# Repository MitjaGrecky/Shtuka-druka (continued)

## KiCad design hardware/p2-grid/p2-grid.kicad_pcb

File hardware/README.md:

# Hardware

KiCad 10 projects. Each board is generated by Python scripts in its `gen/` folder; CI (`.github/workflows/kicad.yml`)
runs ERC, DRC with schematic parity and exports BOM, Gerbers and placement files on every push.
Board map and reasoning: `docs/ru/29_board_map.md`.

| Board | What | Status | Spec |
|---|---|---|---|
| [`m1-screen-knobs`](m1-screen-knobs/) | 8 encoders with touch and 13-LED rings under the screen | rev 0.1, routing (see `UNROUTED`, `QUILTER.md`) | `docs/ru/30_m1_screen_knobs.md` |
| [`bb1-battery`](bb1-battery/) | Battery board: 6 cells, 2 x BQ7791500 (replaces BM, P143-P146) | rev 0.3, placed | `bb1-battery/README.md` |
| [`w1-levels`](w1-levels/) | Volume pots, P48 buttons, window for M5 | rev 0.1, routed | `docs/ru/31_w1_levels.md` |

License: CERN Open Hardware Licence Version 2 - Strongly Reciprocal (CERN-OHL-S-2.0), see `LICENSE`.

Replaced boards are not kept in the tree (P150, 25.11.2026): BM 0.3 (`bm-bms3s`, replaced by BB1, P143, P144) is in the git history only; BB1 carries its protection circuit in `bb1-battery/gen/bm_circuit.py`.

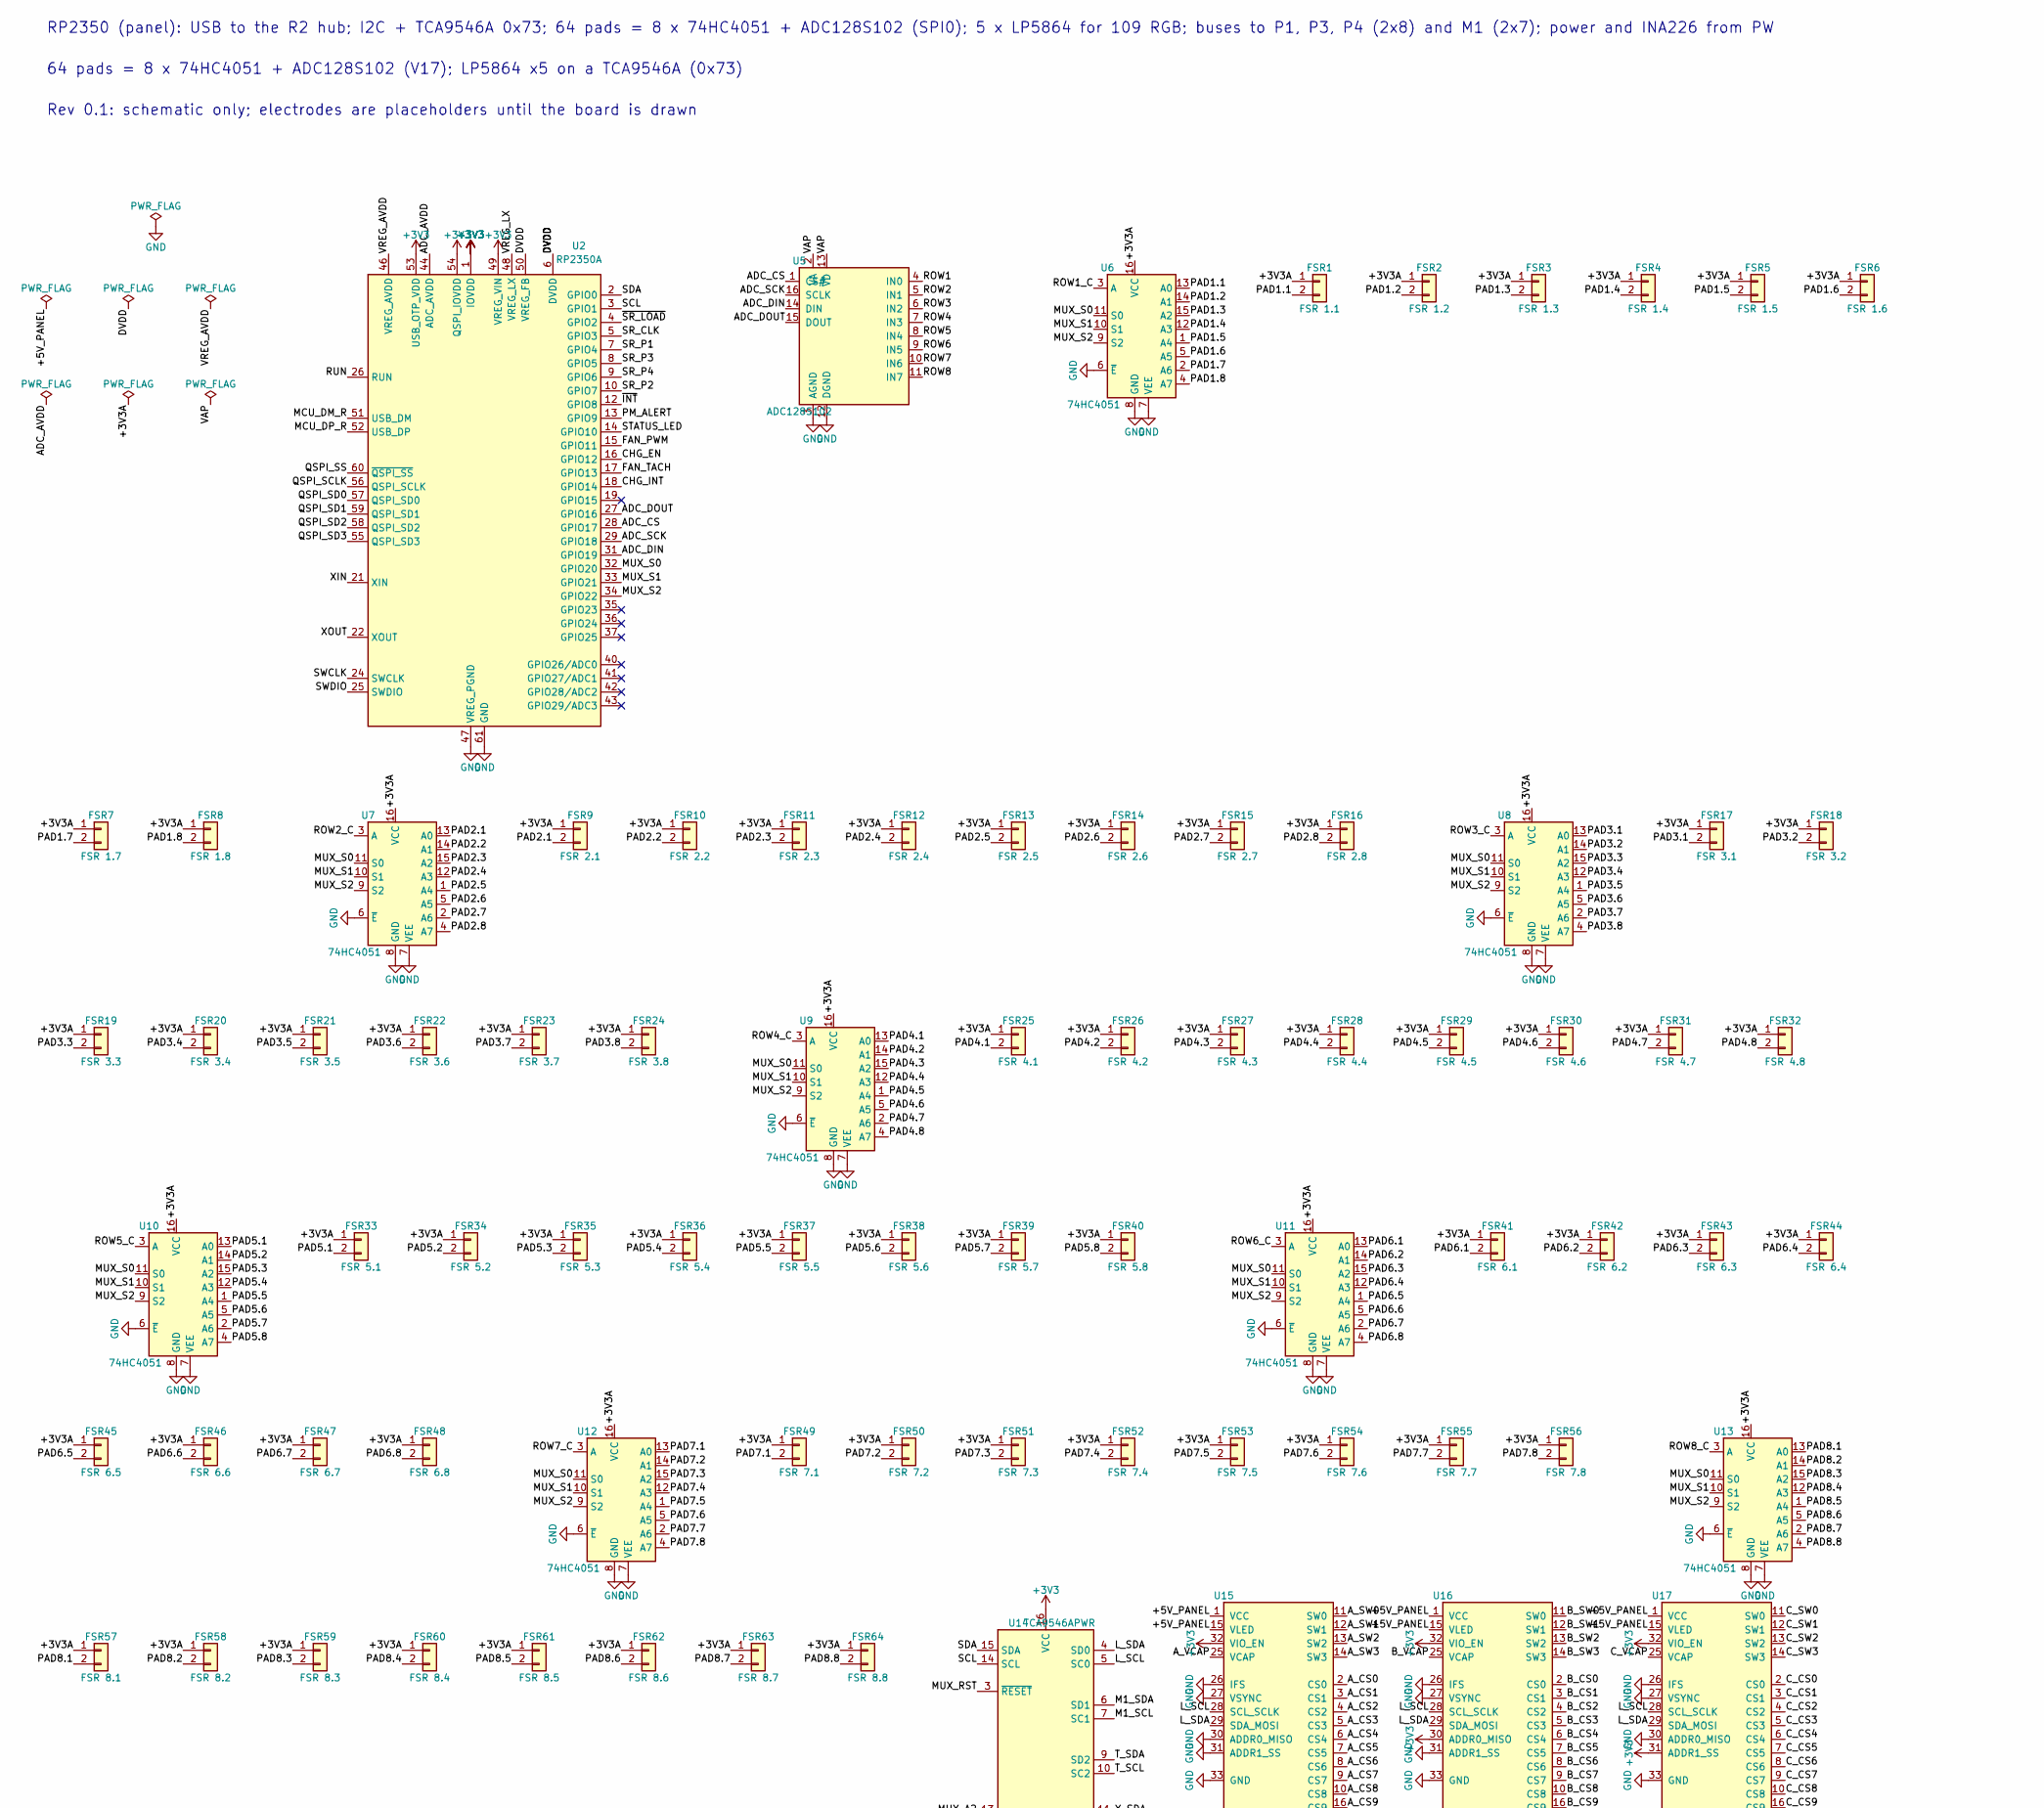
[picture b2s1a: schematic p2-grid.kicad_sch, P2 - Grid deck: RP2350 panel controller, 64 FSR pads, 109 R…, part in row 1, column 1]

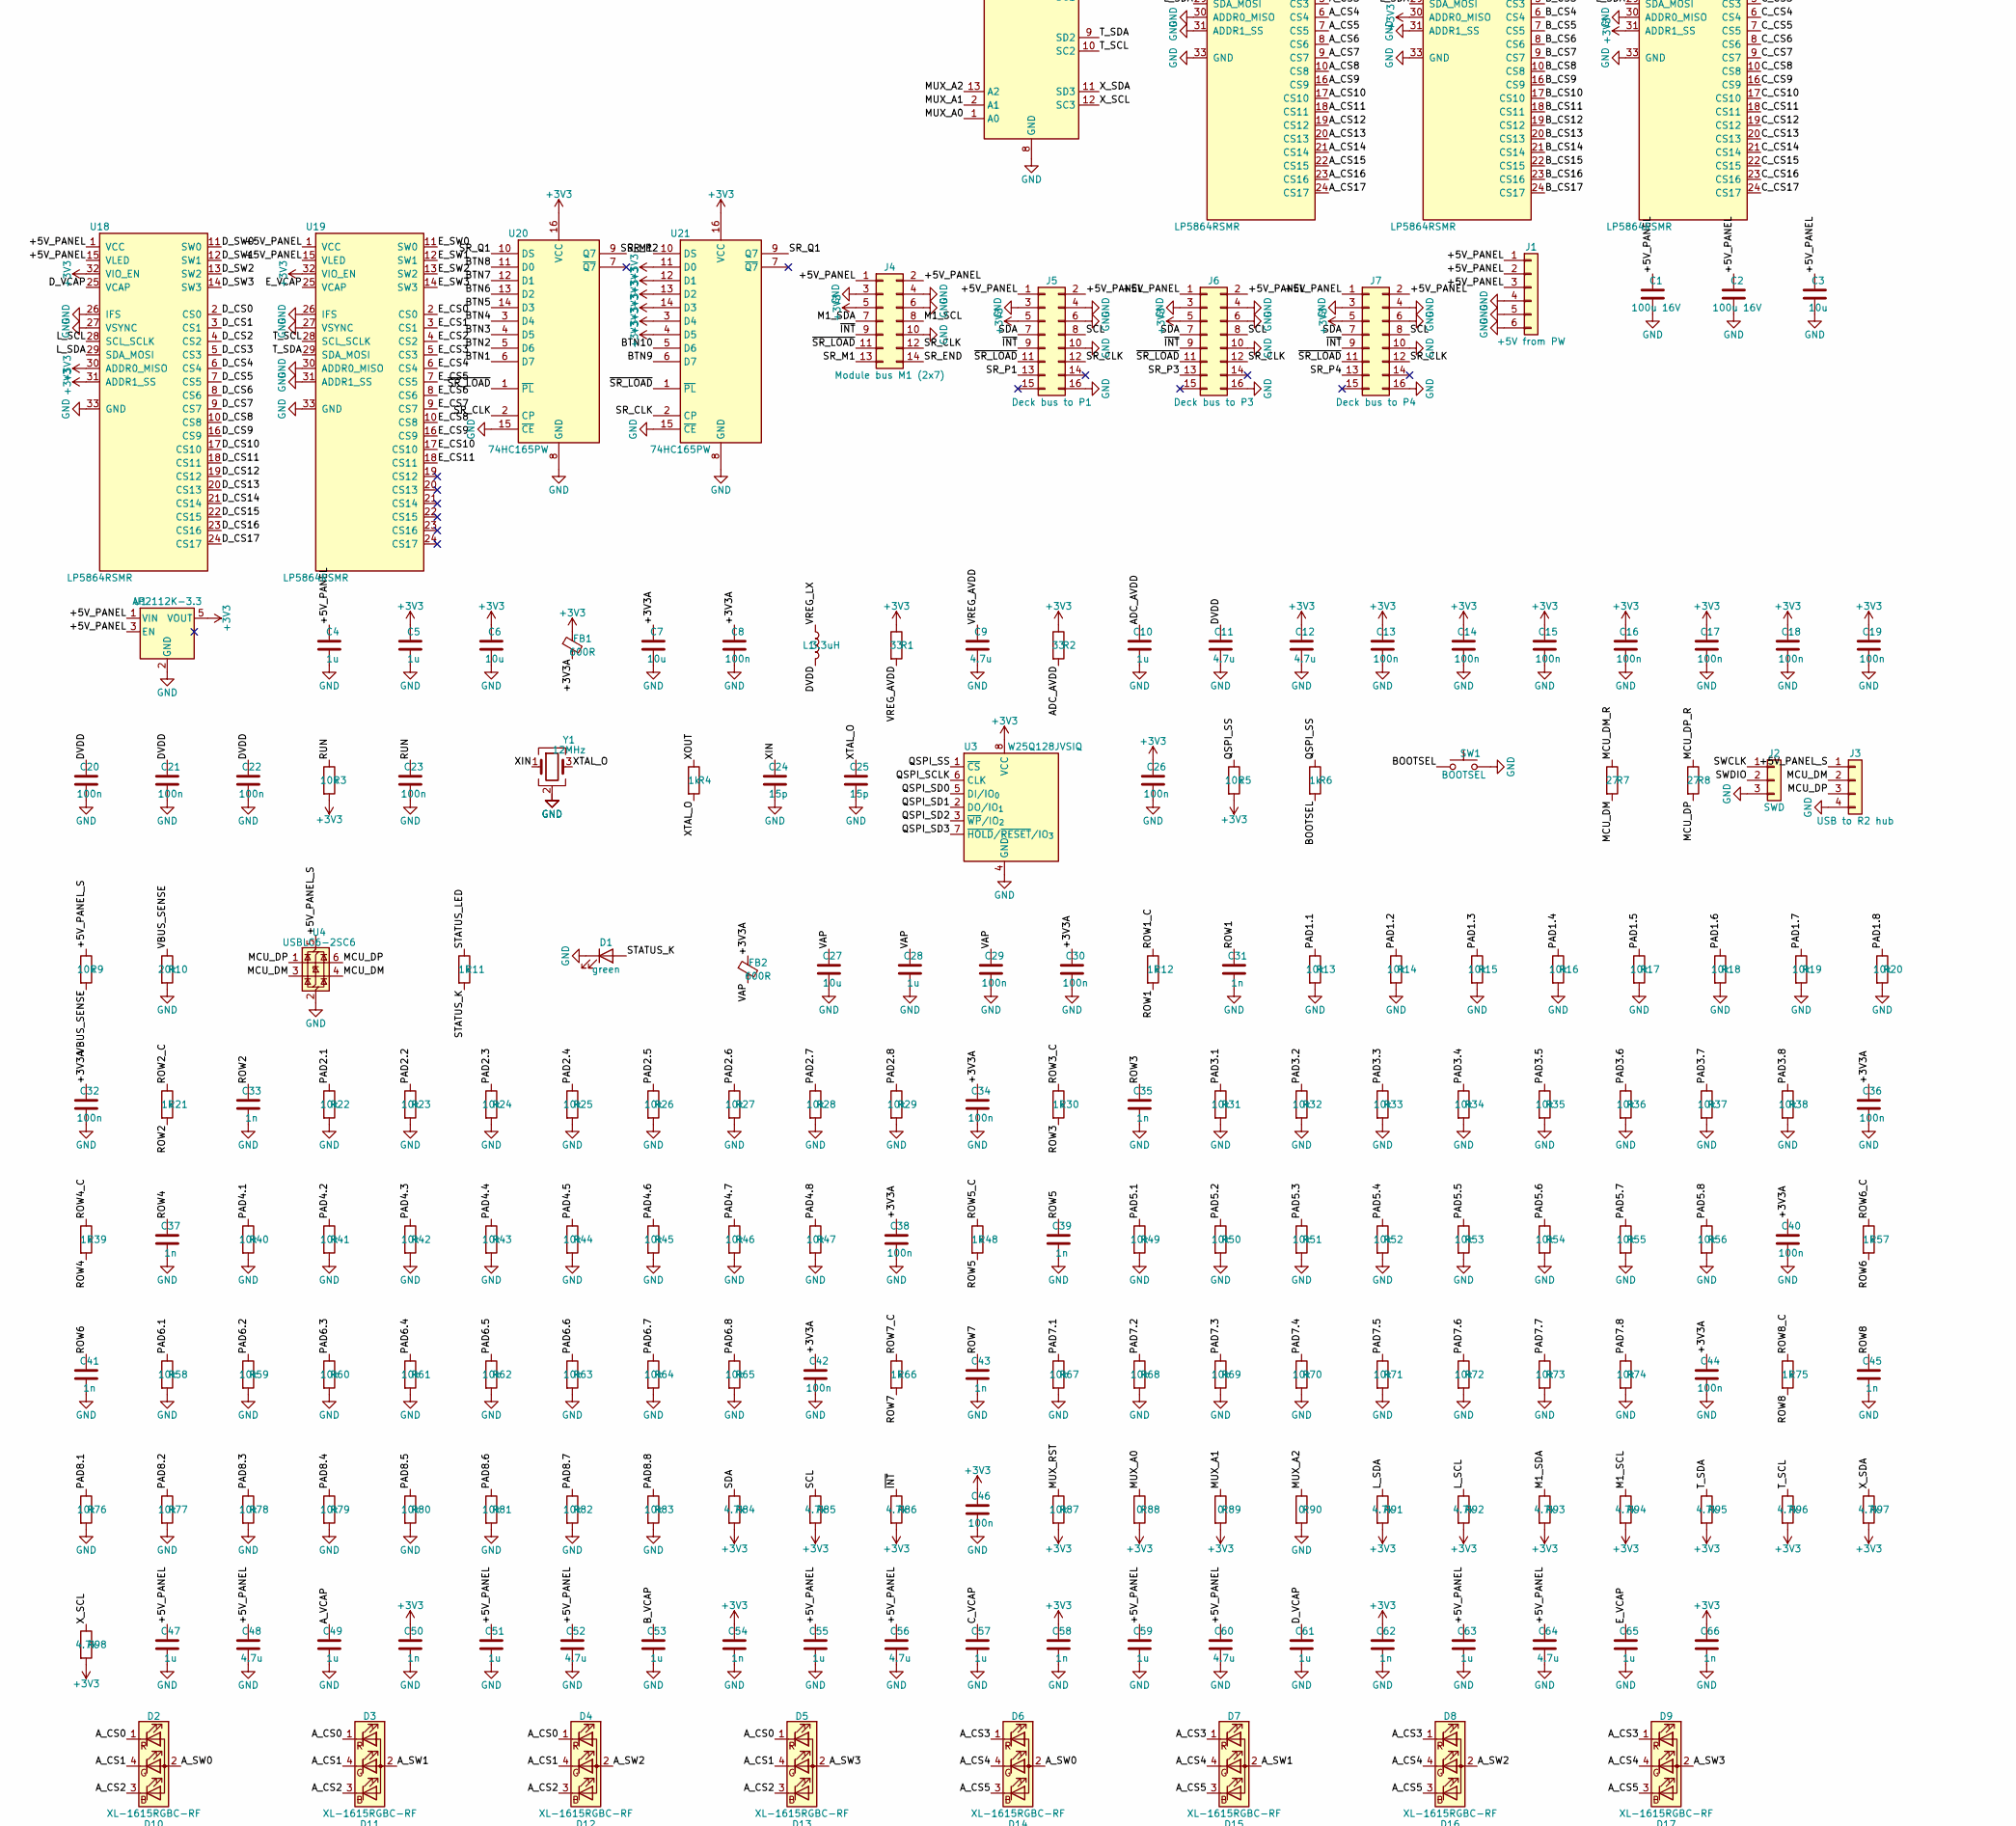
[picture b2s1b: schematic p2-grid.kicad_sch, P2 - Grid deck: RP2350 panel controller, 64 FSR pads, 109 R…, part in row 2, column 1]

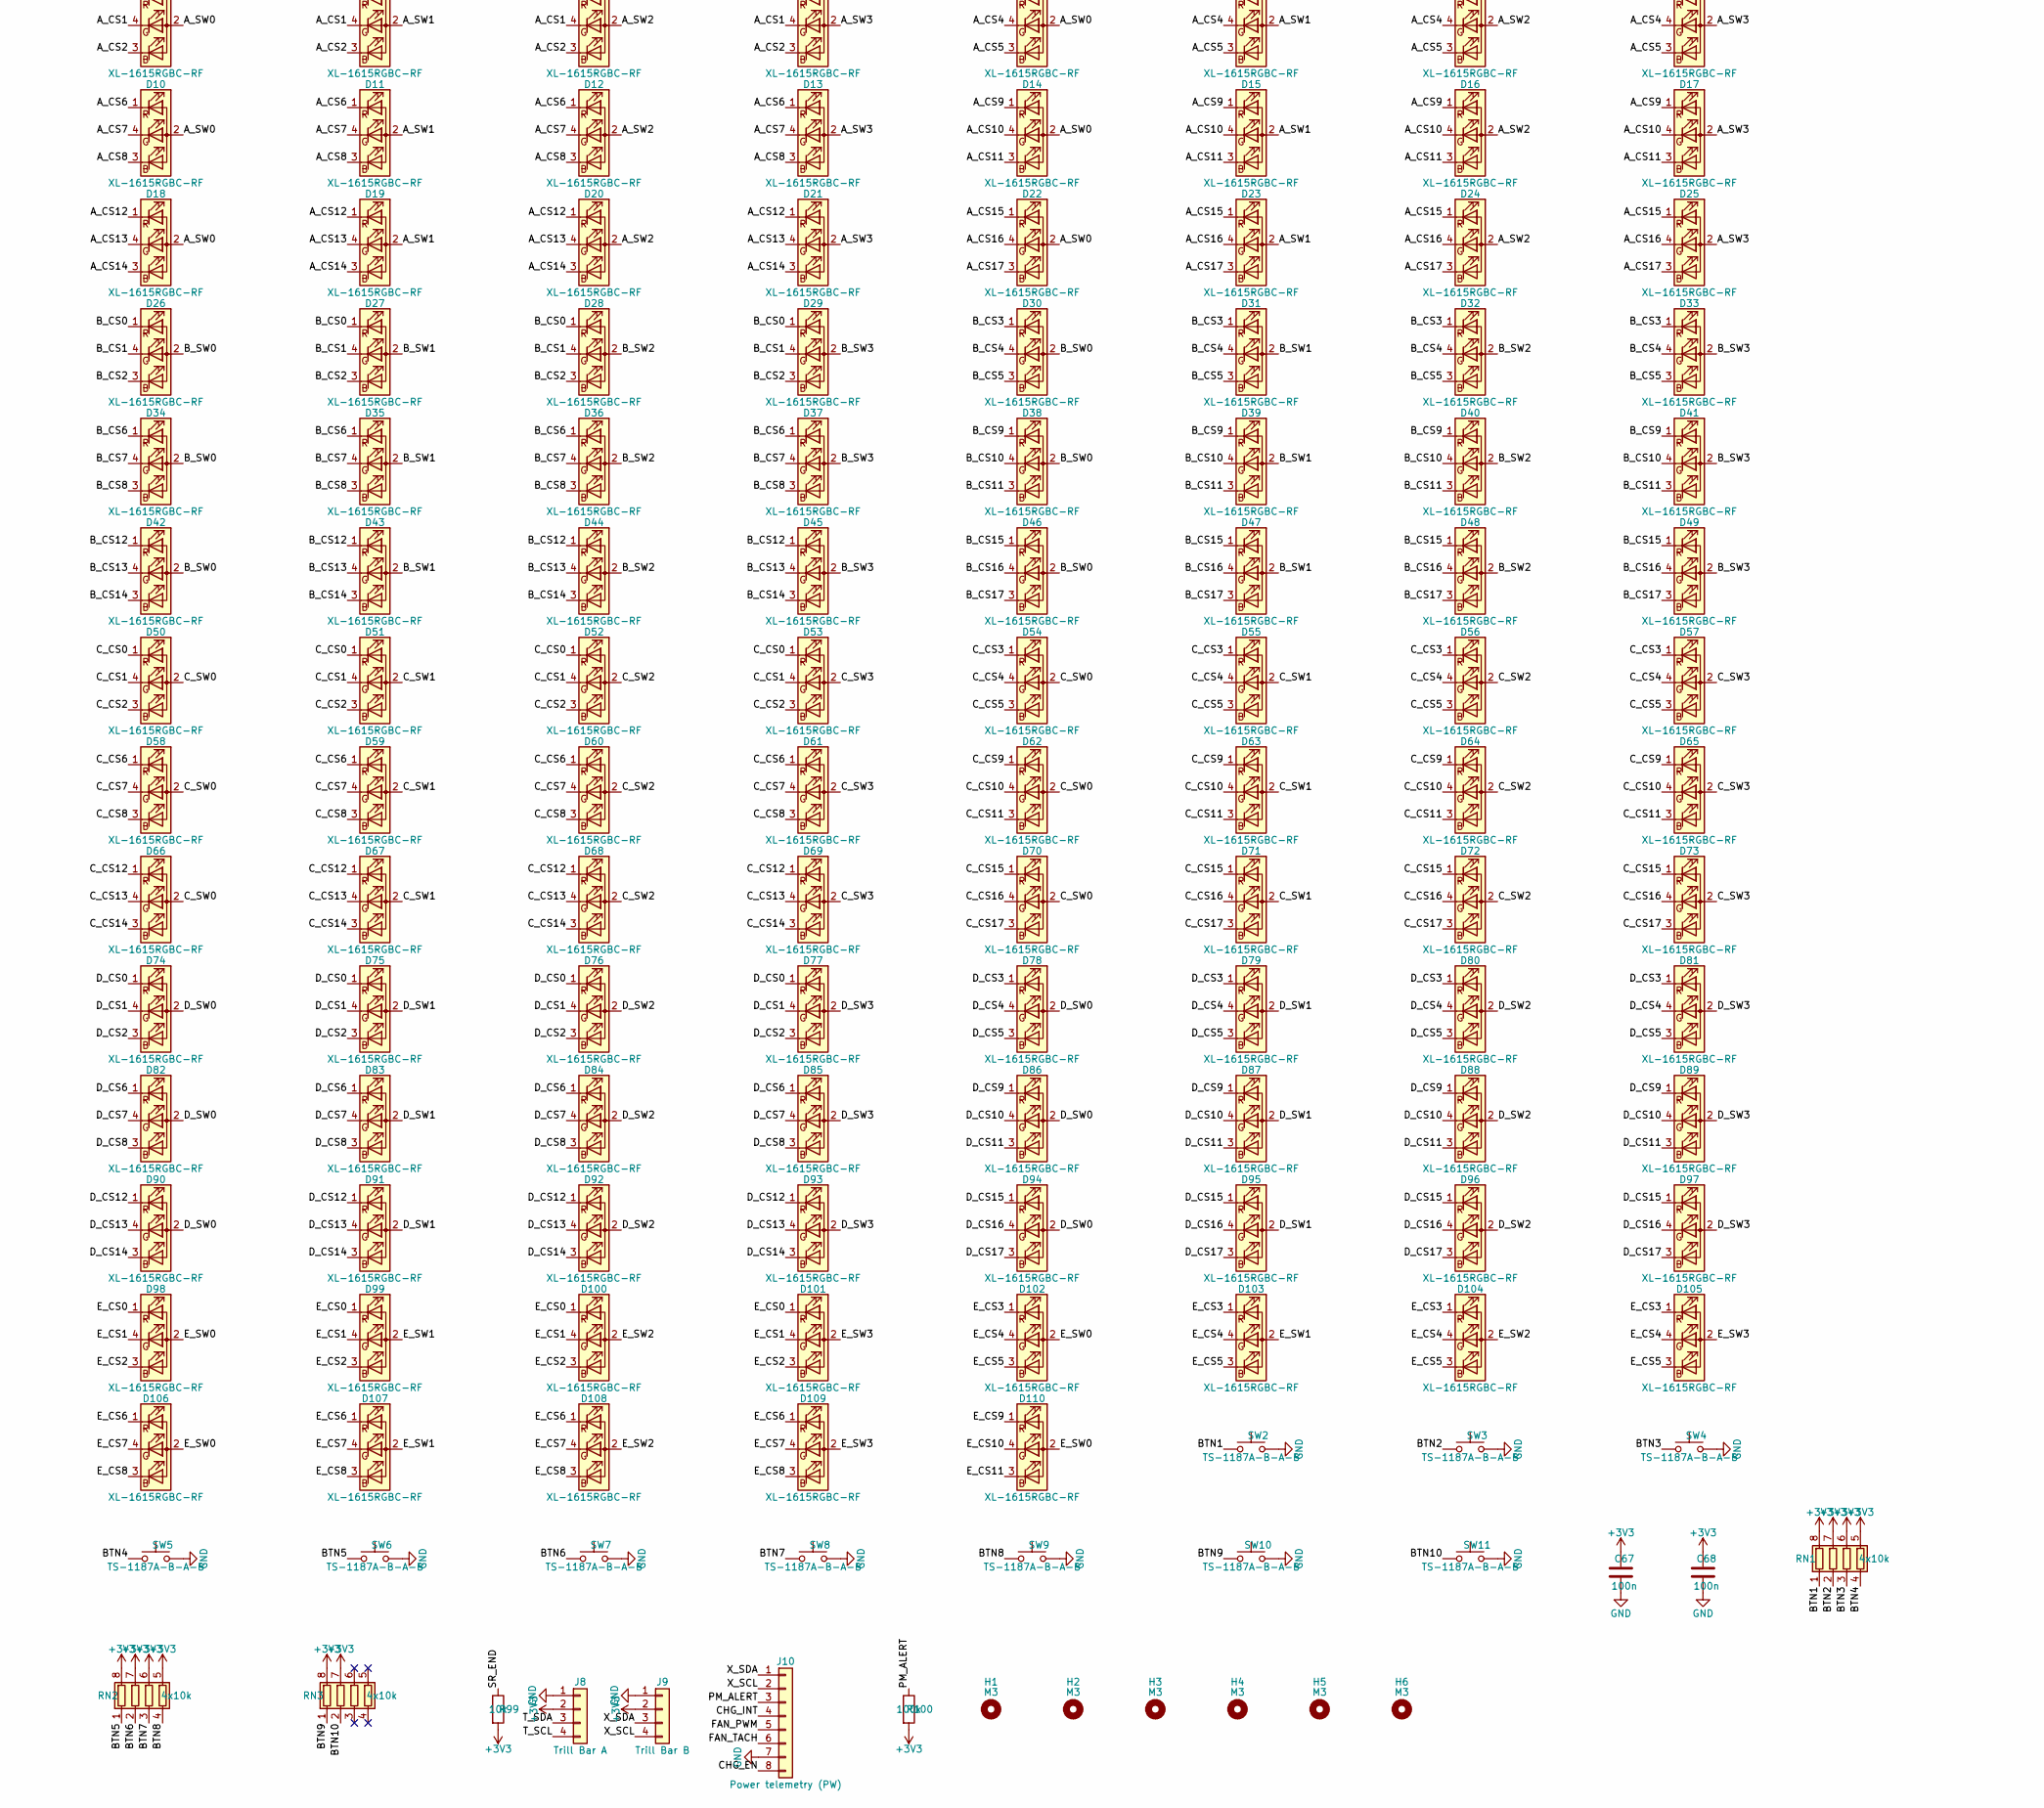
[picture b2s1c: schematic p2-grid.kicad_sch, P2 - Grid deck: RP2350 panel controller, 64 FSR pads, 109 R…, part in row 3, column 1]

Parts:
C1, C2: 100u 16V; CP_Elec_6.3x5.4; LCSC C7469977
C3, C6, C7, C27: 10u; C_0805_2012Metric; LCSC C15850
C4, C5: 1u; C_0603_1608Metric; LCSC C52923
C8, C13, C14, C15, C16, C17, C18, C19, C20, C21, C22, C23, C26, C29, C30, C32, C34, C36, C38, C40, C42, C44, C46, C67, C68: 100n; C_0402_1005Metric; LCSC C1525
C9, C11, C12, C48, C52, C56, C60, C64: 4.7u; C_0805_2012Metric; LCSC C1779
C10, C28, C47, C49, C51, C53, C55, C57, C59, C61, C63, C65: 1u; C_0402_1005Metric; LCSC C52923
C24, C25: 15p; C_0402_1005Metric
C31, C33, C35, C37, C39, C41, C43, C45, C50, C54, C58, C62, C66: 1n; C_0402_1005Metric; LCSC C1523
D1: green; LED_0603_1608Metric; LCSC C84267
D2, D3, D4, D5, D6, D7, D8, D9, D10, D11, D12, D13, D14, D15, D16, D17, D18, D19, D20, D21, D22, D23, D24, D25, D26, D27, D28, D29, D30, D31, D32, D33, D34, D35, D36, D37, D38, D39, D40, D41, D42, D43, D44, D45, D46, D47, D48, D49, D50, D51, D52, D53, D54, D55, D56, D57, D58, D59, D60, D61, D62, D63, D64, D65, D66, D67, D68, D69, D70, D71, D72, D73, D74, D75, D76, D77, D78, D79, D80, D81, D82, D83, D84, D85, D86, D87, D88, D89, D90, D91, D92, D93, D94, D95, D96, D97, D98, D99, D100, D101, D102, D103, D104, D105, D106, D107, D108, D109, D110: XL-1615RGBC-RF; LED_RGB_XL-1615RGBC_1.6x1.5mm; LCSC C965840
FB1, FB2: 600R; R_0603_1608Metric; LCSC C14709
FSR1: FSR 1.1; TestPoint_2Pads_Pitch2.54mm_Drill0.8mm
FSR2: FSR 1.2; TestPoint_2Pads_Pitch2.54mm_Drill0.8mm
FSR3: FSR 1.3; TestPoint_2Pads_Pitch2.54mm_Drill0.8mm
FSR4: FSR 1.4; TestPoint_2Pads_Pitch2.54mm_Drill0.8mm
FSR5: FSR 1.5; TestPoint_2Pads_Pitch2.54mm_Drill0.8mm
FSR6: FSR 1.6; TestPoint_2Pads_Pitch2.54mm_Drill0.8mm
FSR7: FSR 1.7; TestPoint_2Pads_Pitch2.54mm_Drill0.8mm
FSR8: FSR 1.8; TestPoint_2Pads_Pitch2.54mm_Drill0.8mm
FSR9: FSR 2.1; TestPoint_2Pads_Pitch2.54mm_Drill0.8mm
FSR10: FSR 2.2; TestPoint_2Pads_Pitch2.54mm_Drill0.8mm
FSR11: FSR 2.3; TestPoint_2Pads_Pitch2.54mm_Drill0.8mm
FSR12: FSR 2.4; TestPoint_2Pads_Pitch2.54mm_Drill0.8mm
FSR13: FSR 2.5; TestPoint_2Pads_Pitch2.54mm_Drill0.8mm
FSR14: FSR 2.6; TestPoint_2Pads_Pitch2.54mm_Drill0.8mm
FSR15: FSR 2.7; TestPoint_2Pads_Pitch2.54mm_Drill0.8mm
FSR16: FSR 2.8; TestPoint_2Pads_Pitch2.54mm_Drill0.8mm
FSR17: FSR 3.1; TestPoint_2Pads_Pitch2.54mm_Drill0.8mm
FSR18: FSR 3.2; TestPoint_2Pads_Pitch2.54mm_Drill0.8mm
FSR19: FSR 3.3; TestPoint_2Pads_Pitch2.54mm_Drill0.8mm
FSR20: FSR 3.4; TestPoint_2Pads_Pitch2.54mm_Drill0.8mm
FSR21: FSR 3.5; TestPoint_2Pads_Pitch2.54mm_Drill0.8mm
FSR22: FSR 3.6; TestPoint_2Pads_Pitch2.54mm_Drill0.8mm
FSR23: FSR 3.7; TestPoint_2Pads_Pitch2.54mm_Drill0.8mm
FSR24: FSR 3.8; TestPoint_2Pads_Pitch2.54mm_Drill0.8mm
FSR25: FSR 4.1; TestPoint_2Pads_Pitch2.54mm_Drill0.8mm
FSR26: FSR 4.2; TestPoint_2Pads_Pitch2.54mm_Drill0.8mm
FSR27: FSR 4.3; TestPoint_2Pads_Pitch2.54mm_Drill0.8mm
FSR28: FSR 4.4; TestPoint_2Pads_Pitch2.54mm_Drill0.8mm
FSR29: FSR 4.5; TestPoint_2Pads_Pitch2.54mm_Drill0.8mm
FSR30: FSR 4.6; TestPoint_2Pads_Pitch2.54mm_Drill0.8mm
FSR31: FSR 4.7; TestPoint_2Pads_Pitch2.54mm_Drill0.8mm
FSR32: FSR 4.8; TestPoint_2Pads_Pitch2.54mm_Drill0.8mm
FSR33: FSR 5.1; TestPoint_2Pads_Pitch2.54mm_Drill0.8mm
FSR34: FSR 5.2; TestPoint_2Pads_Pitch2.54mm_Drill0.8mm
FSR35: FSR 5.3; TestPoint_2Pads_Pitch2.54mm_Drill0.8mm
FSR36: FSR 5.4; TestPoint_2Pads_Pitch2.54mm_Drill0.8mm
FSR37: FSR 5.5; TestPoint_2Pads_Pitch2.54mm_Drill0.8mm
FSR38: FSR 5.6; TestPoint_2Pads_Pitch2.54mm_Drill0.8mm
FSR39: FSR 5.7; TestPoint_2Pads_Pitch2.54mm_Drill0.8mm
FSR40: FSR 5.8; TestPoint_2Pads_Pitch2.54mm_Drill0.8mm
FSR41: FSR 6.1; TestPoint_2Pads_Pitch2.54mm_Drill0.8mm
FSR42: FSR 6.2; TestPoint_2Pads_Pitch2.54mm_Drill0.8mm
FSR43: FSR 6.3; TestPoint_2Pads_Pitch2.54mm_Drill0.8mm
FSR44: FSR 6.4; TestPoint_2Pads_Pitch2.54mm_Drill0.8mm
FSR45: FSR 6.5; TestPoint_2Pads_Pitch2.54mm_Drill0.8mm
FSR46: FSR 6.6; TestPoint_2Pads_Pitch2.54mm_Drill0.8mm
FSR47: FSR 6.7; TestPoint_2Pads_Pitch2.54mm_Drill0.8mm
FSR48: FSR 6.8; TestPoint_2Pads_Pitch2.54mm_Drill0.8mm
FSR49: FSR 7.1; TestPoint_2Pads_Pitch2.54mm_Drill0.8mm
FSR50: FSR 7.2; TestPoint_2Pads_Pitch2.54mm_Drill0.8mm
FSR51: FSR 7.3; TestPoint_2Pads_Pitch2.54mm_Drill0.8mm
FSR52: FSR 7.4; TestPoint_2Pads_Pitch2.54mm_Drill0.8mm
FSR53: FSR 7.5; TestPoint_2Pads_Pitch2.54mm_Drill0.8mm
FSR54: FSR 7.6; TestPoint_2Pads_Pitch2.54mm_Drill0.8mm
FSR55: FSR 7.7; TestPoint_2Pads_Pitch2.54mm_Drill0.8mm
FSR56: FSR 7.8; TestPoint_2Pads_Pitch2.54mm_Drill0.8mm
FSR57: FSR 8.1; TestPoint_2Pads_Pitch2.54mm_Drill0.8mm
FSR58: FSR 8.2; TestPoint_2Pads_Pitch2.54mm_Drill0.8mm
FSR59: FSR 8.3; TestPoint_2Pads_Pitch2.54mm_Drill0.8mm
FSR60: FSR 8.4; TestPoint_2Pads_Pitch2.54mm_Drill0.8mm
FSR61: FSR 8.5; TestPoint_2Pads_Pitch2.54mm_Drill0.8mm
FSR62: FSR 8.6; TestPoint_2Pads_Pitch2.54mm_Drill0.8mm
FSR63: FSR 8.7; TestPoint_2Pads_Pitch2.54mm_Drill0.8mm
FSR64: FSR 8.8; TestPoint_2Pads_Pitch2.54mm_Drill0.8mm
H1, H2, H3, H4, H5, H6: M3; MountingHole_3.2mm_M3_ISO7380
J1: +5V from PW; Molex_Micro-Fit_3.0_43650-0600_1x06_P3.00mm_Horizontal; LCSC C492352
J2: SWD; JST_PH_S3B-PH-K_1x03_P2.00mm_Horizontal; LCSC C157929
J3: USB to R2 hub; JST_PH_S4B-PH-K_1x04_P2.00mm_Horizontal; LCSC C157926
J4: Module bus M1 (2x7); PinHeader_2x07_P1.27mm_Horizontal; LCSC C22438113
J5: Deck bus to P1; PinHeader_2x08_P1.27mm_Horizontal; LCSC C22438114
J6: Deck bus to P3; PinHeader_2x08_P1.27mm_Horizontal; LCSC C22438114
J7: Deck bus to P4; PinHeader_2x08_P1.27mm_Horizontal; LCSC C22438114
J8: Trill Bar A; JST_PH_S4B-PH-K_1x04_P2.00mm_Horizontal; LCSC C157926
J9: Trill Bar B; JST_PH_S4B-PH-K_1x04_P2.00mm_Horizontal; LCSC C157926
J10: Power telemetry (PW); JST_PH_S8B-PH-K_1x08_P2.00mm_Horizontal
L1: 3.3uH; L_Abracon_AOTA-B201610S; LCSC C42411119
R1, R2: 33; R_0402_1005Metric
R3, R5, R9, R13, R14, R15, R16, R17, R18, R19, R20, R22, R23, R24, R25, R26, R27, R28, R29, R31, R32, R33, R34, R35, R36, R37, R38, R40, R41, R42, R43, R44, R45, R46, R47, R49, R50, R51, R52, R53, R54, R55, R56, R58, R59, R60, R61, R62, R63, R64, R65, R67, R68, R69, R70, R71, R72, R73, R74, R76, R77, R78, R79, R80, R81, R82, R83, R87, R99: 10k; R_0402_1005Metric; LCSC C25744
R4, R6, R11, R12, R21, R30, R39, R48, R57, R66, R75: 1k; R_0402_1005Metric; LCSC C11702
R7, R8: 27; R_0402_1005Metric
R10: 20k; R_0402_1005Metric
R84, R85, R86, R91, R92, R93, R94, R95, R96, R97, R98: 4.7k; R_0402_1005Metric; LCSC C25900
R88, R89, R90: 0; R_0402_1005Metric; LCSC C17168
R100: 100k; R_0402_1005Metric
RN1, RN2, RN3: 4x10k; R_Array_Convex_4x0402; LCSC C25725
SW1: BOOTSEL; SW_Push_1P1T_XKB_TS-1187A; LCSC C318884
SW2, SW3, SW4, SW5, SW6, SW7, SW8, SW9, SW10, SW11: TS-1187A-B-A-B; SW_Push_1P1T_XKB_TS-1187A; LCSC C318884
U1: AP2112K-3.3; SOT-23-5; LCSC C51118
U2: RP2350A; QFN-60-1EP_7x7mm_P0.4mm_EP3.4x3.4mm; LCSC C42411118
U3: W25Q128JVSIQ; SOIC-8_5.3x5.3mm_P1.27mm; LCSC C97521
U4: USBLC6-2SC6; SOT-23-6; LCSC C7519
U5: ADC128S102; TSSOP-16_4.4x5mm_P0.65mm; LCSC C206503
U6, U7, U8, U9, U10, U11, U12, U13: 74HC4051; TSSOP-16_4.4x5mm_P0.65mm; LCSC C5645
U14: TCA9546APWR; TSSOP-16_4.4x5mm_P0.65mm; LCSC C201653
U15, U16, U17, U18, U19: LP5864RSMR; VQFN-32-1EP_4x4mm_P0.4mm_EP2.8x2.8mm; LCSC C5220564
U20, U21: 74HC165PW; TSSOP-16_4.4x5mm_P0.65mm; LCSC C80696
Y1: 12MHz; Crystal_SMD_3225-4Pin_3.2x2.5mm; LCSC C20625731

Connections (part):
+3V3: C5.1, C6.1, C12.1, C13.1, C14.1, C15.1, C16.1, C17.1, C18.1, C19.1, C26.1, C46.1, C50.1, C54.1, C58.1, C62.1, C66.1, C67.1, C68.1, FB1.1, J4.5, J5.5, J6.5, J7.5, J8.2, J9.2, R1.1, R2.1, R3.2, R5.2, R84.2, R85.2, R86.2, R87.2, R88.2, R89.2, R91.2, R92.2, R93.2, R94.2, R95.2, R96.2, R97.2, R98.2, R99.2, R100.2, RN1.5 (R4.2), RN1.6 (R3.2), RN1.7 (R2.2), RN1.8 (R1.2), RN2.5 (R4.2), RN2.6 (R3.2), RN2.7 (R2.2), RN2.8 (R1.2), RN3.7 (R2.2), RN3.8 (R1.2), U1.5 (VOUT), U2.1 (IOVDD), U2.11 (IOVDD), U2.20 (IOVDD), U2.30 (IOVDD), U2.38 (IOVDD), U2.45 (IOVDD), U2.49 (VREG_VIN), U2.53 (USB_OTP_VDD), U2.54 (QSPI_IOVDD), U3.8 (VCC), U14.16 (VCC), U15.32 (VIO_EN), U16.30 (ADDR0_MISO), U16.32 (VIO_EN), U17.31 (ADDR1_SS), U17.32 (VIO_EN), U18.30 (ADDR0_MISO), U18.31 (ADDR1_SS), U18.32 (VIO_EN), U19.32 (VIO_EN), U20.16 (VCC), U21.3 (D4), U21.4 (D5), U21.11 (D0)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
/+3V3A: C7.1, C8.1, C30.1, C32.1, C34.1, C36.1, C38.1, C40.1, C42.1, C44.1, FB1.2, FB2.1, FSR1.1, FSR2.1, FSR3.1, FSR4.1, FSR5.1, FSR6.1, FSR7.1, FSR8.1, FSR9.1, FSR10.1, FSR11.1, FSR12.1, FSR13.1, FSR14.1, FSR15.1, FSR16.1, FSR17.1, FSR18.1, FSR19.1, FSR20.1, FSR21.1, FSR22.1, FSR23.1, FSR24.1, FSR25.1, FSR26.1, FSR27.1, FSR28.1, FSR29.1, FSR30.1, FSR31.1, FSR32.1, FSR33.1, FSR34.1, FSR35.1, FSR36.1, FSR37.1, FSR38.1, FSR39.1, FSR40.1, FSR41.1, FSR42.1, FSR43.1, FSR44.1, FSR45.1, FSR46.1, FSR47.1, FSR48.1, FSR49.1, FSR50.1, FSR51.1, FSR52.1, FSR53.1, FSR54.1, FSR55.1, FSR56.1, FSR57.1, FSR58.1, FSR59.1, FSR60.1, FSR61.1, FSR62.1, FSR63.1, FSR64.1, U6.16 (VCC), U7.16 (VCC), U8.16 (VCC), U9.16 (VCC), U10.16 (VCC)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
/+5V_PANEL: C1.1, C2.1, C3.1, C4.1, C47.1, C48.1, C51.1, C52.1, C55.1, C56.1, C59.1, C60.1, C63.1, C64.1, J1.1, J1.2, J1.3, J4.1, J4.2, J5.1, J5.2, J6.1, J6.2, J7.1, J7.2, U1.1 (VIN), U1.3 (EN), U15.1 (VCC), U15.15 (VLED), U16.1 (VCC), U16.15 (VLED), U17.1 (VCC), U17.15 (VLED), U18.1 (VCC), U18.15 (VLED), U19.1 (VCC), U19.15 (VLED)
/+5V_PANEL_S: J3.1, R9.1, U4.5 (VBUS)
/ADC_AVDD: C10.1, R2.2, U2.44 (ADC_AVDD)
/ADC_CS: U2.28 (GPIO17), U5.1 (CS#)
/ADC_DIN: U2.31 (GPIO19), U5.14 (DIN)
/ADC_DOUT: U2.27 (GPIO16), U5.15 (DOUT)
/ADC_SCK: U2.29 (GPIO18), U5.16 (SCLK)
/A_CS0: D2.1 (RK), D3.1 (RK), D4.1 (RK), D5.1 (RK), U15.2 (CS0)
/A_CS1: D2.4 (GK), D3.4 (GK), D4.4 (GK), D5.4 (GK), U15.3 (CS1)
/A_CS2: D2.3 (BK), D3.3 (BK), D4.3 (BK), D5.3 (BK), U15.4 (CS2)
/A_CS3: D6.1 (RK), D7.1 (RK), D8.1 (RK), D9.1 (RK), U15.5 (CS3)
/A_CS4: D6.4 (GK), D7.4 (GK), D8.4 (GK), D9.4 (GK), U15.6 (CS4)
/A_CS5: D6.3 (BK), D7.3 (BK), D8.3 (BK), D9.3 (BK), U15.7 (CS5)
/A_CS6: D10.1 (RK), D11.1 (RK), D12.1 (RK), D13.1 (RK), U15.8 (CS6)
/A_CS7: D10.4 (GK), D11.4 (GK), D12.4 (GK), D13.4 (GK), U15.9 (CS7)
/A_CS8: D10.3 (BK), D11.3 (BK), D12.3 (BK), D13.3 (BK), U15.10 (CS8)
/A_CS9: D14.1 (RK), D15.1 (RK), D16.1 (RK), D17.1 (RK), U15.16 (CS9)
/A_CS10: D14.4 (GK), D15.4 (GK), D16.4 (GK), D17.4 (GK), U15.17 (CS10)
/A_CS11: D14.3 (BK), D15.3 (BK), D16.3 (BK), D17.3 (BK), U15.18 (CS11)
/A_CS12: D18.1 (RK), D19.1 (RK), D20.1 (RK), D21.1 (RK), U15.19 (CS12)
/A_CS13: D18.4 (GK), D19.4 (GK), D20.4 (GK), D21.4 (GK), U15.20 (CS13)
/A_CS14: D18.3 (BK), D19.3 (BK), D20.3 (BK), D21.3 (BK), U15.21 (CS14)
/A_CS15: D22.1 (RK), D23.1 (RK), D24.1 (RK), D25.1 (RK), U15.22 (CS15)
/A_CS16: D22.4 (GK), D23.4 (GK), D24.4 (GK), D25.4 (GK), U15.23 (CS16)
/A_CS17: D22.3 (BK), D23.3 (BK), D24.3 (BK), D25.3 (BK), U15.24 (CS17)
/A_SW0: D2.2 (A), D6.2 (A), D10.2 (A), D14.2 (A), D18.2 (A), D22.2 (A), U15.11 (SW0)
/A_SW1: D3.2 (A), D7.2 (A), D11.2 (A), D15.2 (A), D19.2 (A), D23.2 (A), U15.12 (SW1)
/A_SW2: D4.2 (A), D8.2 (A), D12.2 (A), D16.2 (A), D20.2 (A), D24.2 (A), U15.13 (SW2)
/A_SW3: D5.2 (A), D9.2 (A), D13.2 (A), D17.2 (A), D21.2 (A), D25.2 (A), U15.14 (SW3)
/A_VCAP: C49.1, U15.25 (VCAP)
/BOOTSEL: R6.2, SW1.1
/BTN1: RN1.1 (R1.1), SW2.1, U20.6 (D7)
/BTN2: RN1.2 (R2.1), SW3.1, U20.5 (D6)
/BTN3: RN1.3 (R3.1), SW4.1, U20.4 (D5)
/BTN4: RN1.4 (R4.1), SW5.1, U20.3 (D4)
/BTN5: RN2.1 (R1.1), SW6.1, U20.14 (D3)
/BTN6: RN2.2 (R2.1), SW7.1, U20.13 (D2)
/BTN7: RN2.3 (R3.1), SW8.1, U20.12 (D1)
/BTN8: RN2.4 (R4.1), SW9.1, U20.11 (D0)
/BTN9: RN3.1 (R1.1), SW10.1, U21.6 (D7)
/BTN10: RN3.2 (R2.1), SW11.1, U21.5 (D6)
/B_CS0: D26.1 (RK), D27.1 (RK), D28.1 (RK), D29.1 (RK), U16.2 (CS0)
/B_CS1: D26.4 (GK), D27.4 (GK), D28.4 (GK), D29.4 (GK), U16.3 (CS1)
/B_CS2: D26.3 (BK), D27.3 (BK), D28.3 (BK), D29.3 (BK), U16.4 (CS2)
/B_CS3: D30.1 (RK), D31.1 (RK), D32.1 (RK), D33.1 (RK), U16.5 (CS3)
/B_CS4: D30.4 (GK), D31.4 (GK), D32.4 (GK), D33.4 (GK), U16.6 (CS4)
/B_CS5: D30.3 (BK), D31.3 (BK), D32.3 (BK), D33.3 (BK), U16.7 (CS5)
/B_CS6: D34.1 (RK), D35.1 (RK), D36.1 (RK), D37.1 (RK), U16.8 (CS6)
/B_CS7: D34.4 (GK), D35.4 (GK), D36.4 (GK), D37.4 (GK), U16.9 (CS7)
/B_CS8: D34.3 (BK), D35.3 (BK), D36.3 (BK), D37.3 (BK), U16.10 (CS8)
/B_CS9: D38.1 (RK), D39.1 (RK), D40.1 (RK), D41.1 (RK), U16.16 (CS9)
/B_CS10: D38.4 (GK), D39.4 (GK), D40.4 (GK), D41.4 (GK), U16.17 (CS10)
/B_CS11: D38.3 (BK), D39.3 (BK), D40.3 (BK), D41.3 (BK), U16.18 (CS11)
/B_CS12: D42.1 (RK), D43.1 (RK), D44.1 (RK), D45.1 (RK), U16.19 (CS12)
/B_CS13: D42.4 (GK), D43.4 (GK), D44.4 (GK), D45.4 (GK), U16.20 (CS13)
/B_CS14: D42.3 (BK), D43.3 (BK), D44.3 (BK), D45.3 (BK), U16.21 (CS14)
/B_CS15: D46.1 (RK), D47.1 (RK), D48.1 (RK), D49.1 (RK), U16.22 (CS15)
/B_CS16: D46.4 (GK), D47.4 (GK), D48.4 (GK), D49.4 (GK), U16.23 (CS16)
/B_CS17: D46.3 (BK), D47.3 (BK), D48.3 (BK), D49.3 (BK), U16.24 (CS17)
/B_SW0: D26.2 (A), D30.2 (A), D34.2 (A), D38.2 (A), D42.2 (A), D46.2 (A), U16.11 (SW0)
/B_SW1: D27.2 (A), D31.2 (A), D35.2 (A), D39.2 (A), D43.2 (A), D47.2 (A), U16.12 (SW1)
/B_SW2: D28.2 (A), D32.2 (A), D36.2 (A), D40.2 (A), D44.2 (A), D48.2 (A), U16.13 (SW2)
/B_SW3: D29.2 (A), D33.2 (A), D37.2 (A), D41.2 (A), D45.2 (A), D49.2 (A), U16.14 (SW3)
/B_VCAP: C53.1, U16.25 (VCAP)
/CHG_EN: J10.8, U2.16 (GPIO12)
/CHG_INT: J10.4, U2.18 (GPIO14)
/C_CS0: D50.1 (RK), D51.1 (RK), D52.1 (RK), D53.1 (RK), U17.2 (CS0)
/C_CS1: D50.4 (GK), D51.4 (GK), D52.4 (GK), D53.4 (GK), U17.3 (CS1)
/C_CS2: D50.3 (BK), D51.3 (BK), D52.3 (BK), D53.3 (BK), U17.4 (CS2)
/C_CS3: D54.1 (RK), D55.1 (RK), D56.1 (RK), D57.1 (RK), U17.5 (CS3)
/C_CS4: D54.4 (GK), D55.4 (GK), D56.4 (GK), D57.4 (GK), U17.6 (CS4)
/C_CS5: D54.3 (BK), D55.3 (BK), D56.3 (BK), D57.3 (BK), U17.7 (CS5)
/C_CS6: D58.1 (RK), D59.1 (RK), D60.1 (RK), D61.1 (RK), U17.8 (CS6)
/C_CS7: D58.4 (GK), D59.4 (GK), D60.4 (GK), D61.4 (GK), U17.9 (CS7)
/C_CS8: D58.3 (BK), D59.3 (BK), D60.3 (BK), D61.3 (BK), U17.10 (CS8)
/C_CS9: D62.1 (RK), D63.1 (RK), D64.1 (RK), D65.1 (RK), U17.16 (CS9)
/C_CS10: D62.4 (GK), D63.4 (GK), D64.4 (GK), D65.4 (GK), U17.17 (CS10)
/C_CS11: D62.3 (BK), D63.3 (BK), D64.3 (BK), D65.3 (BK), U17.18 (CS11)
/C_CS12: D66.1 (RK), D67.1 (RK), D68.1 (RK), D69.1 (RK), U17.19 (CS12)
/C_CS13: D66.4 (GK), D67.4 (GK), D68.4 (GK), D69.4 (GK), U17.20 (CS13)
/C_CS14: D66.3 (BK), D67.3 (BK), D68.3 (BK), D69.3 (BK), U17.21 (CS14)
/C_CS15: D70.1 (RK), D71.1 (RK), D72.1 (RK), D73.1 (RK), U17.22 (CS15)
/C_CS16: D70.4 (GK), D71.4 (GK), D72.4 (GK), D73.4 (GK), U17.23 (CS16)
/C_CS17: D70.3 (BK), D71.3 (BK), D72.3 (BK), D73.3 (BK), U17.24 (CS17)
/C_SW0: D50.2 (A), D54.2 (A), D58.2 (A), D62.2 (A), D66.2 (A), D70.2 (A), U17.11 (SW0)
/C_SW1: D51.2 (A), D55.2 (A), D59.2 (A), D63.2 (A), D67.2 (A), D71.2 (A), U17.12 (SW1)
/C_SW2: D52.2 (A), D56.2 (A), D60.2 (A), D64.2 (A), D68.2 (A), D72.2 (A), U17.13 (SW2)
/C_SW3: D53.2 (A), D57.2 (A), D61.2 (A), D65.2 (A), D69.2 (A), D73.2 (A), U17.14 (SW3)
/C_VCAP: C57.1, U17.25 (VCAP)
/DVDD: C11.1, C20.1, C21.1, C22.1, L1.2, U2.6 (DVDD), U2.23 (DVDD), U2.39 (DVDD), U2.50 (VREG_FB)
/D_CS0: D74.1 (RK), D75.1 (RK), D76.1 (RK), D77.1 (RK), U18.2 (CS0)
/D_CS1: D74.4 (GK), D75.4 (GK), D76.4 (GK), D77.4 (GK), U18.3 (CS1)
/D_CS2: D74.3 (BK), D75.3 (BK), D76.3 (BK), D77.3 (BK), U18.4 (CS2)
/D_CS3: D78.1 (RK), D79.1 (RK), D80.1 (RK), D81.1 (RK), U18.5 (CS3)
/D_CS4: D78.4 (GK), D79.4 (GK), D80.4 (GK), D81.4 (GK), U18.6 (CS4)
/D_CS5: D78.3 (BK), D79.3 (BK), D80.3 (BK), D81.3 (BK), U18.7 (CS5)
/D_CS6: D82.1 (RK), D83.1 (RK), D84.1 (RK), D85.1 (RK), U18.8 (CS6)
/D_CS7: D82.4 (GK), D83.4 (GK), D84.4 (GK), D85.4 (GK), U18.9 (CS7)
/D_CS8: D82.3 (BK), D83.3 (BK), D84.3 (BK), D85.3 (BK), U18.10 (CS8)
/D_CS9: D86.1 (RK), D87.1 (RK), D88.1 (RK), D89.1 (RK), U18.16 (CS9)
/D_CS10: D86.4 (GK), D87.4 (GK), D88.4 (GK), D89.4 (GK), U18.17 (CS10)
/D_CS11: D86.3 (BK), D87.3 (BK), D88.3 (BK), D89.3 (BK), U18.18 (CS11)
/D_CS12: D90.1 (RK), D91.1 (RK), D92.1 (RK), D93.1 (RK), U18.19 (CS12)
/D_CS13: D90.4 (GK), D91.4 (GK), D92.4 (GK), D93.4 (GK), U18.20 (CS13)
/D_CS14: D90.3 (BK), D91.3 (BK), D92.3 (BK), D93.3 (BK), U18.21 (CS14)
/D_CS15: D94.1 (RK), D95.1 (RK), D96.1 (RK), D97.1 (RK), U18.22 (CS15)
/D_CS16: D94.4 (GK), D95.4 (GK), D96.4 (GK), D97.4 (GK), U18.23 (CS16)
/D_CS17: D94.3 (BK), D95.3 (BK), D96.3 (BK), D97.3 (BK), U18.24 (CS17)
/D_SW0: D74.2 (A), D78.2 (A), D82.2 (A), D86.2 (A), D90.2 (A), D94.2 (A), U18.11 (SW0)
/D_SW1: D75.2 (A), D79.2 (A), D83.2 (A), D87.2 (A), D91.2 (A), D95.2 (A), U18.12 (SW1)
/D_SW2: D76.2 (A), D80.2 (A), D84.2 (A), D88.2 (A), D92.2 (A), D96.2 (A), U18.13 (SW2)
/D_SW3: D77.2 (A), D81.2 (A), D85.2 (A), D89.2 (A), D93.2 (A), D97.2 (A), U18.14 (SW3)
/D_VCAP: C61.1, U18.25 (VCAP)
/E_CS0: D98.1 (RK), D99.1 (RK), D100.1 (RK), D101.1 (RK), U19.2 (CS0)
/E_CS1: D98.4 (GK), D99.4 (GK), D100.4 (GK), D101.4 (GK), U19.3 (CS1)
/E_CS2: D98.3 (BK), D99.3 (BK), D100.3 (BK), D101.3 (BK), U19.4 (CS2)
/E_CS3: D102.1 (RK), D103.1 (RK), D104.1 (RK), D105.1 (RK), U19.5 (CS3)
/E_CS4: D102.4 (GK), D103.4 (GK), D104.4 (GK), D105.4 (GK), U19.6 (CS4)
/E_CS5: D102.3 (BK), D103.3 (BK), D104.3 (BK), D105.3 (BK), U19.7 (CS5)
/E_CS6: D106.1 (RK), D107.1 (RK), D108.1 (RK), D109.1 (RK), U19.8 (CS6)
/E_CS7: D106.4 (GK), D107.4 (GK), D108.4 (GK), D109.4 (GK), U19.9 (CS7)
/E_CS8: D106.3 (BK), D107.3 (BK), D108.3 (BK), D109.3 (BK), U19.10 (CS8)
/E_CS9: D110.1 (RK), U19.16 (CS9)
/E_CS10: D110.4 (GK), U19.17 (CS10)
/E_CS11: D110.3 (BK), U19.18 (CS11)
/E_SW0: D98.2 (A), D102.2 (A), D106.2 (A), D110.2 (A), U19.11 (SW0)
/E_SW1: D99.2 (A), D103.2 (A), D107.2 (A), U19.12 (SW1)
/E_SW2: D100.2 (A), D104.2 (A), D108.2 (A), U19.13 (SW2)
/E_SW3: D101.2 (A), D105.2 (A), D109.2 (A), U19.14 (SW3)
/E_VCAP: C65.1, U19.25 (VCAP)
/FAN_PWM: J10.5, U2.15 (GPIO11)
/FAN_TACH: J10.6, U2.17 (GPIO13)
/L_SCL: R92.1, U14.5 (SC0), U15.28 (SCL_SCLK), U16.28 (SCL_SCLK), U17.28 (SCL_SCLK), U18.28 (SCL_SCLK)
/L_SDA: R91.1, U14.4 (SD0), U15.29 (SDA_MOSI), U16.29 (SDA_MOSI), U17.29 (SDA_MOSI), U18.29 (SDA_MOSI)
/M1_SCL: J4.8, R94.1, U14.7 (SC1)
/M1_SDA: J4.7, R93.1, U14.6 (SD1)
/MCU_DM: J3.2, R7.2, U4.3 (I/O2), U4.4 (I/O2)
/MCU_DM_R: R7.1, U2.51 (USB_DM)
/MCU_DP: J3.3, R8.2, U4.1 (I/O1), U4.6 (I/O1)
/MCU_DP_R: R8.1, U2.52 (USB_DP)
/MUX_A0: R88.1, U14.1 (A0)
/MUX_A1: R89.1, U14.2 (A1)
/MUX_A2: R90.1, U14.13 (A2)
/MUX_RST: R87.1, U14.3 (~RESET)
/MUX_S0: U2.32 (GPIO20), U6.11 (S0), U7.11 (S0), U8.11 (S0), U9.11 (S0), U10.11 (S0), U11.11 (S0), U12.11 (S0), U13.11 (S0)
/MUX_S1: U2.33 (GPIO21), U6.10 (S1), U7.10 (S1), U8.10 (S1), U9.10 (S1), U10.10 (S1), U11.10 (S1), U12.10 (S1), U13.10 (S1)
/MUX_S2: U2.34 (GPIO22), U6.9 (S2), U7.9 (S2), U8.9 (S2), U9.9 (S2), U10.9 (S2), U11.9 (S2), U12.9 (S2), U13.9 (S2)
/PAD1.1: FSR1.2, R13.1, U6.13 (A0)
/PAD1.2: FSR2.2, R14.1, U6.14 (A1)
/PAD1.3: FSR3.2, R15.1, U6.15 (A2)
/PAD1.4: FSR4.2, R16.1, U6.12 (A3)
/PAD1.5: FSR5.2, R17.1, U6.1 (A4)
/PAD1.6: FSR6.2, R18.1, U6.5 (A5)
/PAD1.7: FSR7.2, R19.1, U6.2 (A6)
/PAD1.8: FSR8.2, R20.1, U6.4 (A7)
/PAD2.1: FSR9.2, R22.1, U7.13 (A0)
/PAD2.2: FSR10.2, R23.1, U7.14 (A1)
/PAD2.3: FSR11.2, R24.1, U7.15 (A2)
/PAD2.4: FSR12.2, R25.1, U7.12 (A3)
/PAD2.5: FSR13.2, R26.1, U7.1 (A4)
/PAD2.6: FSR14.2, R27.1, U7.5 (A5)
/PAD2.7: FSR15.2, R28.1, U7.2 (A6)
/PAD2.8: FSR16.2, R29.1, U7.4 (A7)
/PAD3.1: FSR17.2, R31.1, U8.13 (A0)
/PAD3.2: FSR18.2, R32.1, U8.14 (A1)
/PAD3.3: FSR19.2, R33.1, U8.15 (A2)
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
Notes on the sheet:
RP2350 (panel): USB to the R2 hub; I2C + TCA9546A 0x73; 64 pads = 8 x 74HC4051 + ADC128S102 (SPI0); 5 x LP5864 for 109 RGB; buses to P1, P3, P4 (2x8) and M1 (2x7); power and INA226 from PW
64 pads = 8 x 74HC4051 + ADC128S102 (V17); LP5864 x5 on a TCA9546A (0x73)
Rev 0.1: schematic only; electrodes are placeholders until the board is drawn

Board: 4 copper layers, 397 parts (208 on the bottom side), 265 nets, no tracks yet.
